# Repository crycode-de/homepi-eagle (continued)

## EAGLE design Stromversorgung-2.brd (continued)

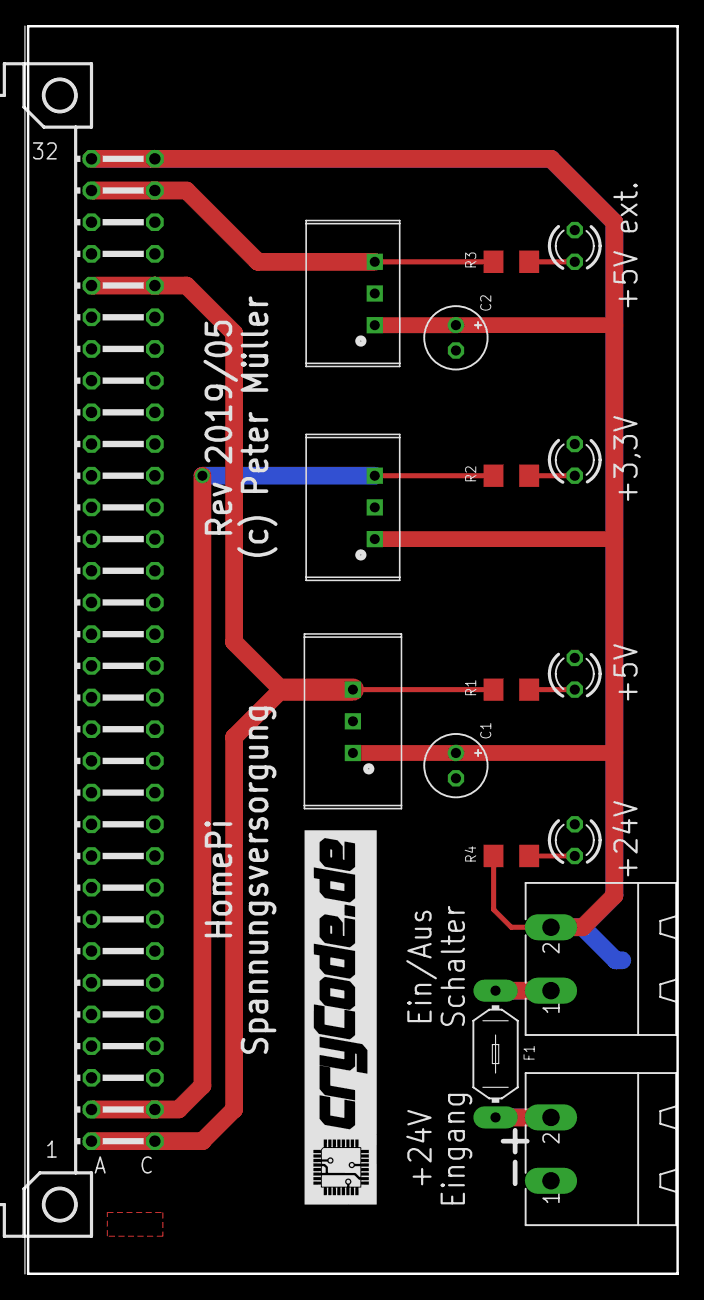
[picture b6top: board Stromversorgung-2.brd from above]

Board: 2 copper layers, 52.1 x 100.0 mm, 19 parts (1 on the bottom side), 11 nets.

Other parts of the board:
U$1: 30MM
